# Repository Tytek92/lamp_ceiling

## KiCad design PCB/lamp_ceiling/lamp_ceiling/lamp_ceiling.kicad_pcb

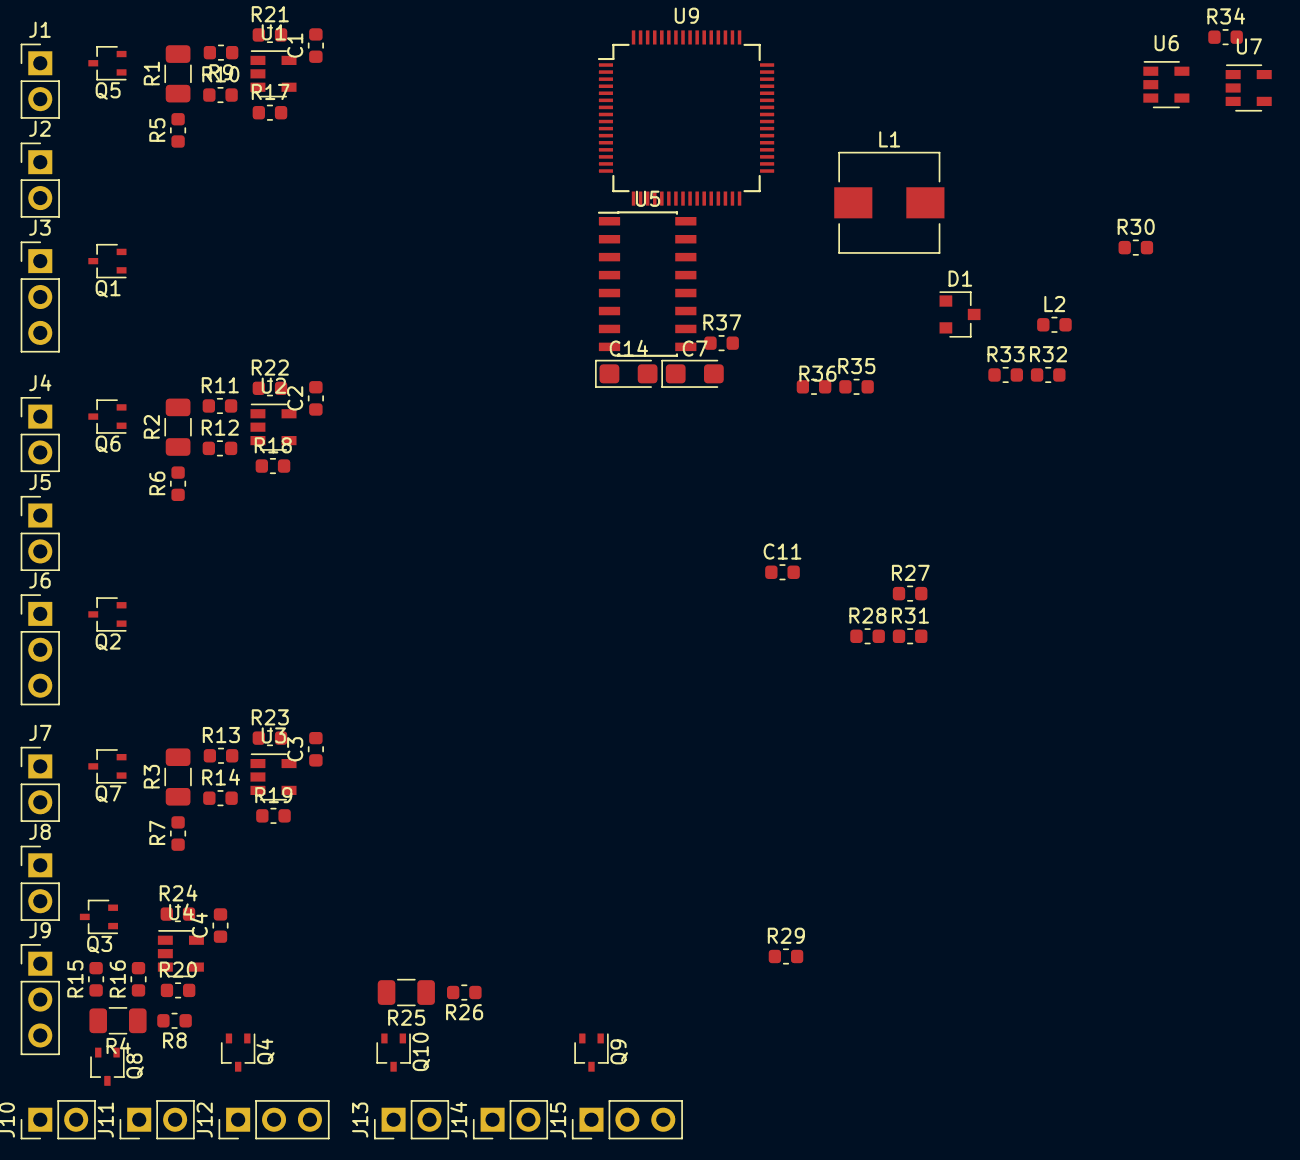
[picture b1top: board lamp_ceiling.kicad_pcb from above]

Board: 2 copper layers, 80 parts (0 on the bottom side), 45 nets.

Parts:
C1, C2, C3, C4, C11: 100nF; C_0603_1608Metric
C7, C14: 33uF; CP_EIA-3216-10_Kemet-I
D1: LM4040BIM3-2.5/NOPB; SOT-23
J1, J4, J7, J10, J13: LED_supply; PinHeader_1x02_P2.54mm_Vertical
J2, J5, J8, J11, J14: LED1_NTC; PinHeader_1x02_P2.54mm_Vertical
J3, J6, J9, J12, J15: LED1_fan; PinHeader_1x03_P2.54mm_Vertical
L1: 22uH; L_Wuerth_HCI-7030
L2: Ferrite_Bead_Small; R_0603_1608Metric
Q1, Q2, Q3, Q4, Q5, Q6, Q7, Q8, Q9, Q10: DMG1012UW-7; SOT-323_SC-70
R1, R2, R3, R4, R25: 1R, 0.25W, 1%; R_1206_3216Metric
R5, R6, R7, R8, R26, R32, R37: 0R; R_0603_1608Metric
R9, R10, R11, R12, R13, R14, R15, R16, R27, R28: 20k, 1%; R_0603_1608Metric
R17, R18, R19, R20, R21, R22, R23, R24, R29, R31: 100k, 1%; R_0603_1608Metric
R30: 47k; R_0603_1608Metric
R33: 100k; R_0603_1608Metric
R34: 52k3R 1%; R_0603_1608Metric
R35: 10k 1%; R_0603_1608Metric
R36: 470R; R_0603_1608Metric
U1, U2, U3, U4, U6: LMV321IDBVR; SOT-23-5
U5: MCP3208; SOIC-16_3.9x9.9mm_P1.27mm
U7: MIC5504-3.3YM5; SOT-23-5
U9: STM32F030R8Tx; LQFP-64_10x10mm_P0.5mm

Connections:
+3V3: C1.1, C2.1, C3.1, C4.1, C11.1, C14.1, J2.2, J5.2, J8.2, J11.2, J14.2, L2.1, U1.5, U2.5, U3.5, U4.5, U6.5, U7.5
+12V: J1.2, J3.2, J4.2, J6.2, J7.2, J9.2, J10.2, J12.2, J13.2, J15.2
/LED1_R+: Q5.2, R1.2, R9.1
/LED2_R+: Q6.2, R2.2, R11.1
/LED3_R+: Q7.2, R3.2, R13.1
/LED4_R+: Q8.2, R4.2, R15.1
/LED5_R+: Q10.2, R25.2, R27.1
GND: C1.2, C2.2, C3.2, C4.2, C7.2, C11.2, C14.2, R21.2, R22.2, R23.2, R24.2, R30.1, R31.2, R32.1, R33.1, R35.1, R37.1, U1.2, U2.2, U3.2, U4.2, U6.2, U7.2
GNDPWR: Q1.2, Q2.2, Q3.2, Q4.2, Q9.2, R5.1, R6.1, R7.1, R8.1, R26.1, R32.2
GNDREF: D1.2, R37.2
LED1_ADC: R17.2, U1.4, U5.1
LED2_ADC: R18.2, U2.4, U5.2
LED3_ADC: R19.2, U3.4, U5.3
LED4_ADC: R20.2, U4.4, U5.4
LED5_ADC: R29.2, U5.5, U6.4
LED_FAN_PWM: Q1.1, Q2.1, Q3.1, Q4.1, Q9.1
unnamed: J1.1, Q5.3
unnamed: J3.1, Q1.3
unnamed: J4.1, Q6.3
unnamed: J6.1, Q2.3
unnamed: J7.1, Q7.3
unnamed: J9.1, Q3.3
unnamed: J10.1, Q8.3
unnamed: J12.1, Q4.3
unnamed: J13.1, Q10.3
unnamed: J15.1, Q9.3
unnamed: L2.2, R36.1
unnamed: R1.1, R5.2, R10.1
unnamed: R10.2, R17.1, U1.3
unnamed: R11.2, R22.1, U2.1
unnamed: R2.1, R6.2, R12.1
unnamed: R12.2, R18.1, U2.3
unnamed: R13.2, R23.1, U3.1
unnamed: R3.1, R7.2, R14.1
unnamed: R14.2, R19.1, U3.3
unnamed: R15.2, R24.1, U4.1
unnamed: R4.1, R8.2, R16.1
unnamed: R16.2, R20.1, U4.3
unnamed: R9.2, R21.1, U1.1
unnamed: R25.1, R26.2, R28.1
unnamed: R27.2, R31.1, U6.1
unnamed: R28.2, R29.1, U6.3
unnamed: R34.1, R35.2
REF_2V5: D1.1, R36.2
fb: C7.1, L1.1, R34.2, U7.1, U7.3

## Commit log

2018-09-04 5 channels for LED schematic started
2018-09-17 dc-dc schematic, Vref
2018-09-17 started layout
